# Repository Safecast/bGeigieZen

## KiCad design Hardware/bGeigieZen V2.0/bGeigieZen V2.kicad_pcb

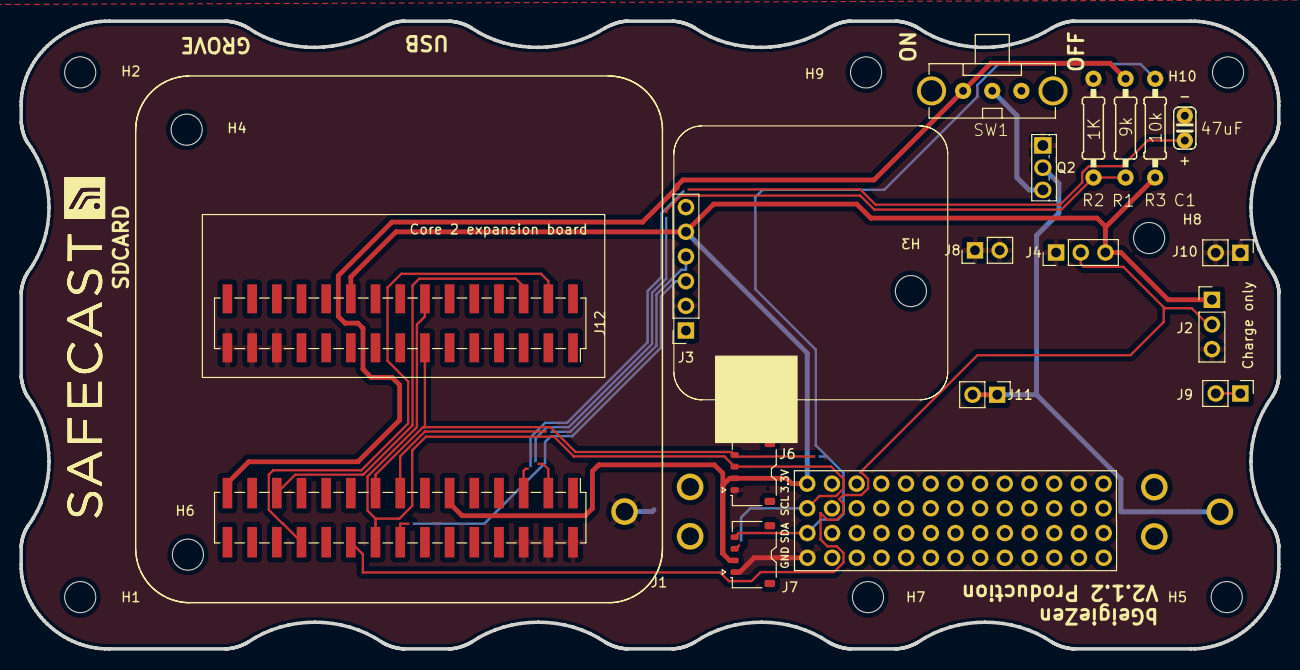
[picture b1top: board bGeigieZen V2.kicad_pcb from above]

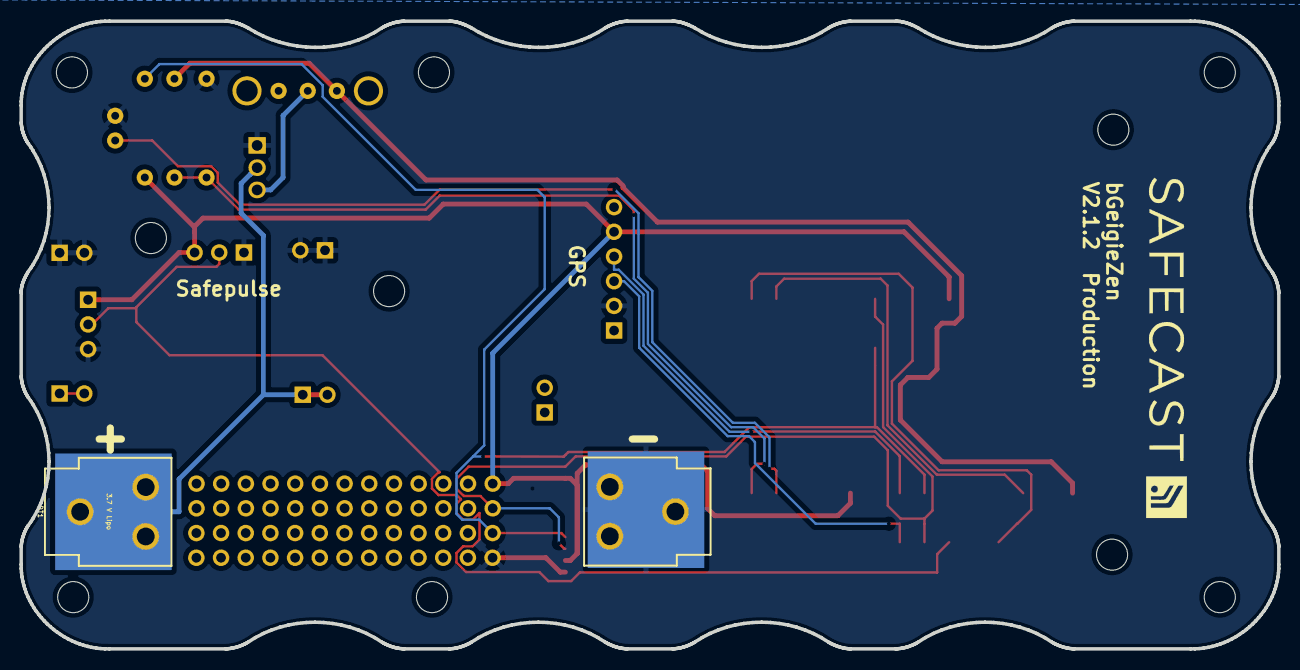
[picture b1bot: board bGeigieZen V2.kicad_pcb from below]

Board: 2 copper layers, 129.4 x 64.6 mm, 31 parts (2 on the bottom side), 15 nets.

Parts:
BT1: 3.7 V Lipo; BATTERY_18650-HOLDER
C1: 47uF; C025-024X044
H1, H2, H3, H4, H5, H6, H7, H8, H9, H10: MountingHole_Pad; MountingHole_3.2mm_M3
J1: M5 2x15 pin; PinHeader_2x15_P2.54mm_Vertical_SMD
J2: Geiger; PinHeader_1x03_P2.54mm_Vertical
J3: GPS; PinSocket_1x06_P2.54mm_Vertical
J4: Geiger 2; PinHeader_1x03_P2.54mm_Vertical
J5: Extra support header; PinHeader_1x02_P2.54mm_Vertical
J6, J7: Grove; JST_ACH_BM04B-ACHSS-A-GAN-ETF_1x04-1MP_P1.20mm_Vertical
J8: QI charger GND; PinHeader_1x02_P2.54mm_Vertical
J9: QI Plus; PinHeader_1x02_P2.54mm_Vertical
J10: QI GND; PinHeader_1x02_P2.54mm_Vertical
J11: QI charger Plus; PinHeader_1x02_P2.54mm_Vertical
J12: M5 2x15 pin; PinSocket_2x15_P2.54mm_Vertical_SMD
Q2: IRFU9024N; TO-251-3_Vertical
R1: 9k; 0207_10
R2: 1K; 0207_10
R3: 10k; 0207_10
SW1: SW_SPDT; EG1206
sea of pads 1, sea of pads 2: PinHeader_2x13_P2.54mm_Vertical

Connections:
3.3V: J1.11, J2.1, J3.5, J4.3, J6.2, J7.2, J12.20, R3.1, sea of pads 1.2
/BAT: J1.29, R1.1, SW1.3 (C)
/GIO2: J1.20, J2.2, J4.2
/GIO34: J1.25, J12.6
/RX2: J1.15, J3.4
/Reset: C1.1, J1.5
/SCL: J1.18, J6.3, J7.3, J12.14, sea of pads 1.1
/SDA: J1.17, J6.4, J7.4, J12.13, R3.2, sea of pads 2.2
/TX2: J1.16, J3.3
/VBATT: Q2.3, SW1.2 (B)
GND: BT1.2 (-), C1.2, J1.2, J1.4, J1.6, J2.3, J3.2, J4.1, J6.1, J7.1, J8.1, J8.2, J10.1, J10.2, J12.25, J12.27, J12.29, Q2.1, R2.2, sea of pads 2.1
unnamed: BT1.1 (+), J11.1, J11.2, Q2.2
unnamed: J1.3, R1.2, R2.1
unnamed: J1.24, J12.4
unnamed: J9.1, J9.2

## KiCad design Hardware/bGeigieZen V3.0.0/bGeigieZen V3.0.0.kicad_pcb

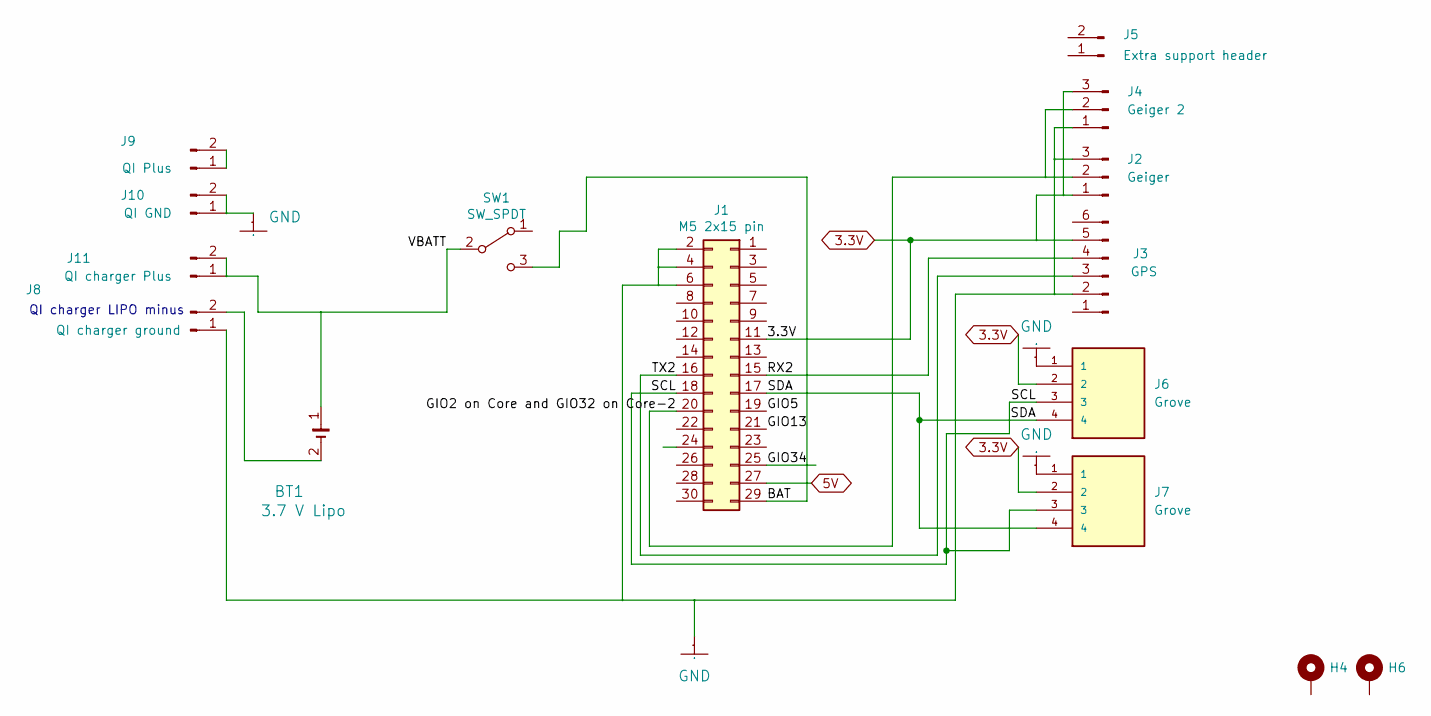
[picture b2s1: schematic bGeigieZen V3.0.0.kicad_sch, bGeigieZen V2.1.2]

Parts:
BT1: 3.7 V Lipo; BATTERY_18650-HOLDER
H4, H6: MountingHole_Pad; MountingHole_3.2mm_M3
J1: M5 2x15 pin; PinHeader_2x15_P2.54mm_Vertical_SMD
J2: Geiger; PinHeader_1x03_P2.54mm_Vertical
J3: GPS; PinSocket_1x06_P2.54mm_Vertical
J4: Geiger 2; PinHeader_1x03_P2.54mm_Vertical
J5: Extra support header; PinHeader_1x02_P2.54mm_Vertical
J6, J7: Grove; JST_ACH_BM04B-ACHSS-A-GAN-ETF_1x04-1MP_P1.20mm_Vertical; PARTREV A
J8: QI charger ground; PinHeader_1x02_P2.54mm_Vertical
J9: QI Plus; PinHeader_1x02_P2.54mm_Vertical
J10: QI GND; PinHeader_1x02_P2.54mm_Vertical
J11: QI charger Plus; PinHeader_1x02_P2.54mm_Vertical_4056
SW1: SW_SPDT; EG1206

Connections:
3.3V: J1.11, J2.1, J3.5, J4.3, J6.2, J7.2
5V: J1.27
/BAT: J1.29, SW1.3 (C)
/GIO2 on Core and GIO32 on Core-2: J1.20, J2.2, J4.2
/GIO5: J1.19
/GIO13: J1.21
/GIO34: J1.25
/RX2: J1.15, J3.4
/SCL: J1.18, J6.3, J7.3
/SDA: J1.17, J6.4, J7.4
/TX2: J1.16, J3.3
/VBATT: BT1.1 (+), J11.1, J11.2, SW1.2 (B)
GND: J1.2, J1.4, J1.6, J2.3, J3.2, J4.1, J6.1, J7.1, J8.1, J10.1, J10.2
unnamed: BT1.2 (-), J8.2
unnamed: J9.1, J9.2

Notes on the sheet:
QI charger LIPO minus

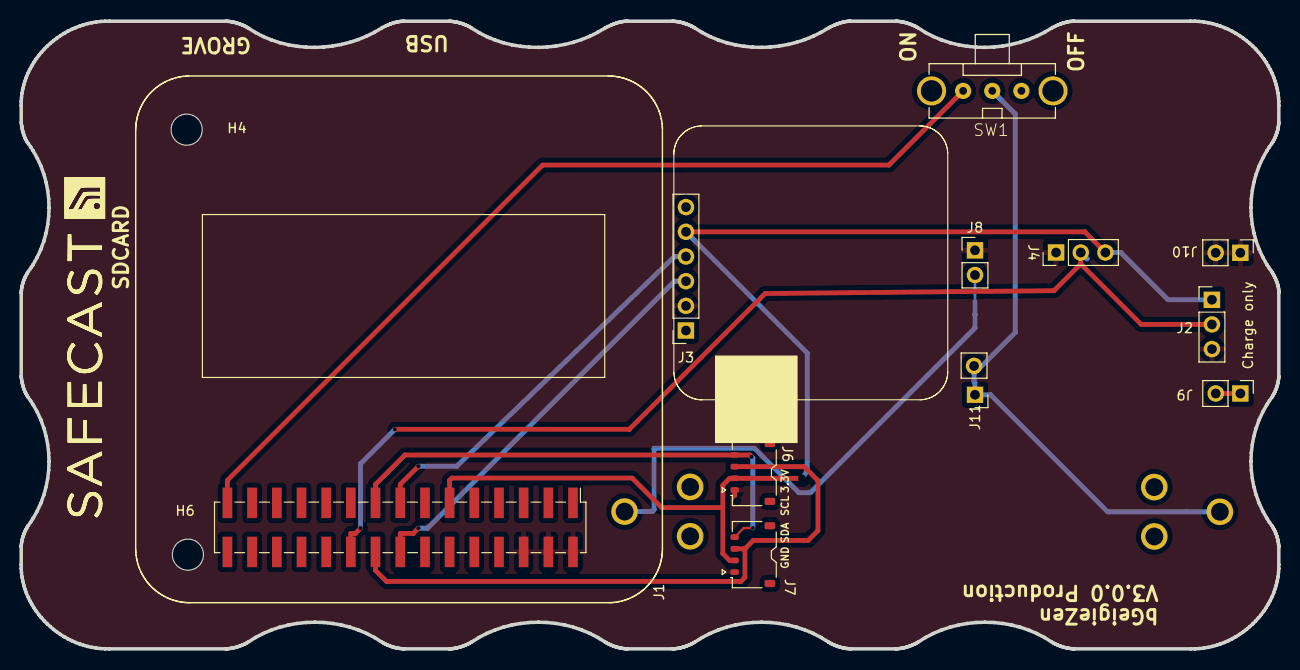
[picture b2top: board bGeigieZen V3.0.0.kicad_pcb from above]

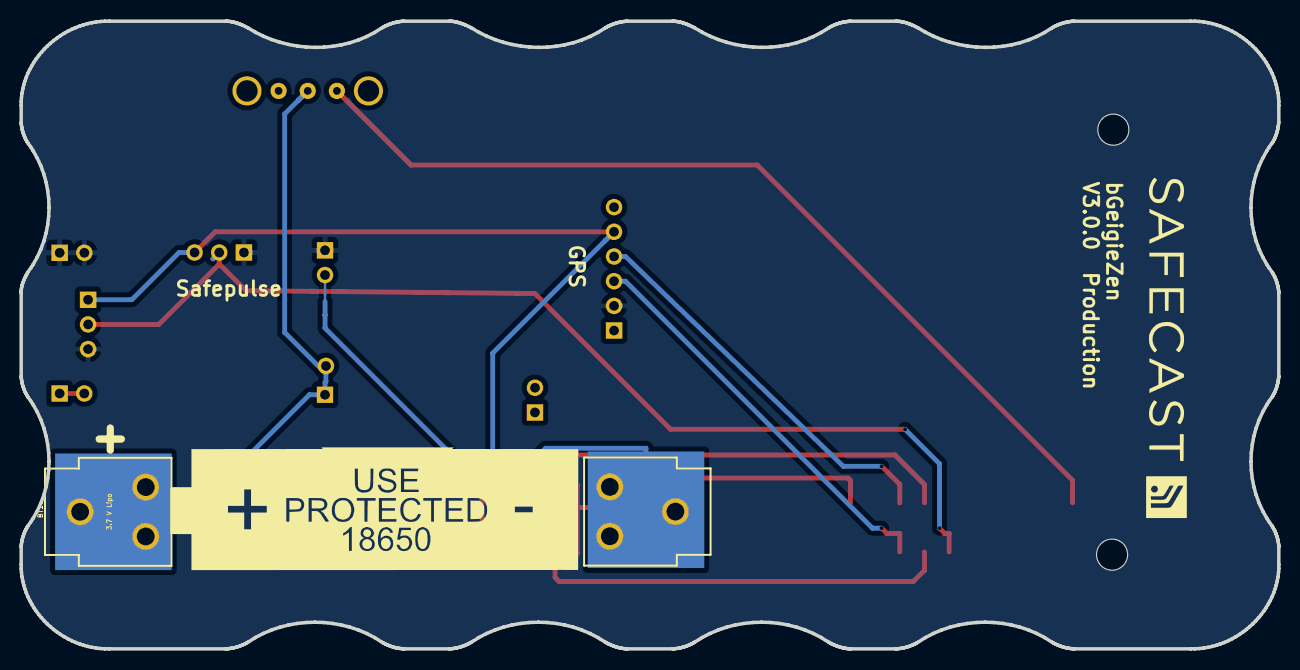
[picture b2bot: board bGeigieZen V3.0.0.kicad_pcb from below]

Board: 2 copper layers, 129.4 x 64.6 mm, 18 parts (3 on the bottom side), 11 nets.

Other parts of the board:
1850 LABEL: LOGO; 18650 map
G back: LOGO
G front: LOGO

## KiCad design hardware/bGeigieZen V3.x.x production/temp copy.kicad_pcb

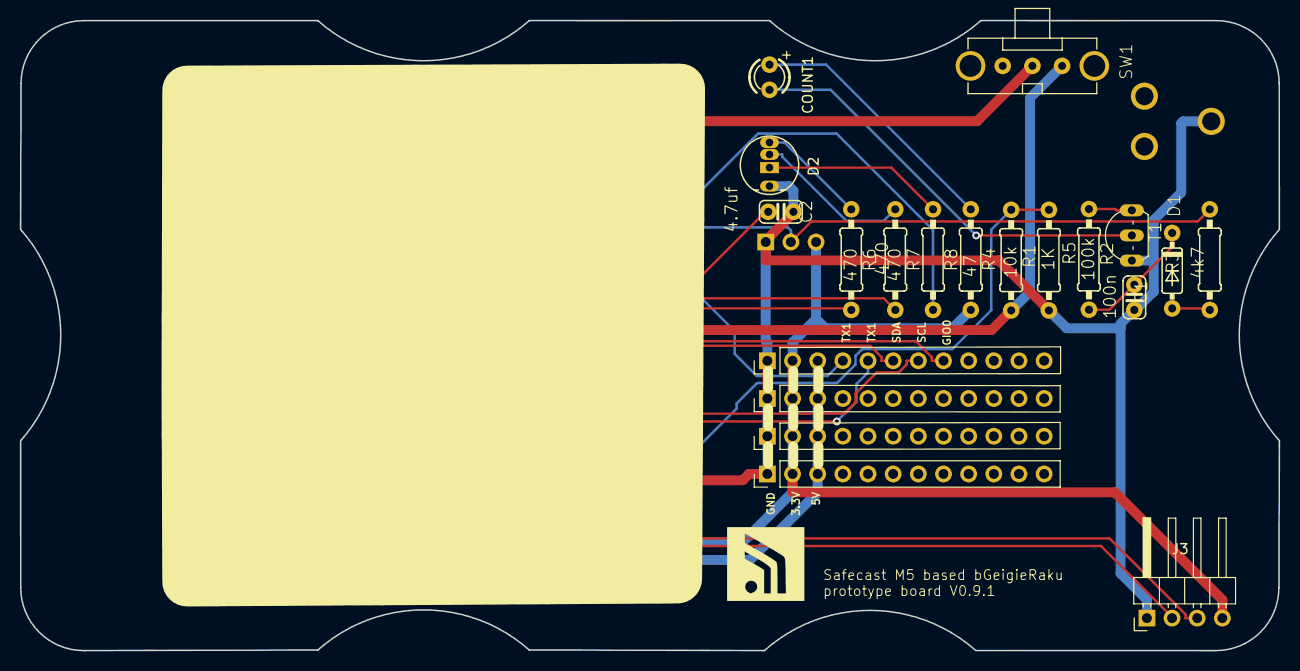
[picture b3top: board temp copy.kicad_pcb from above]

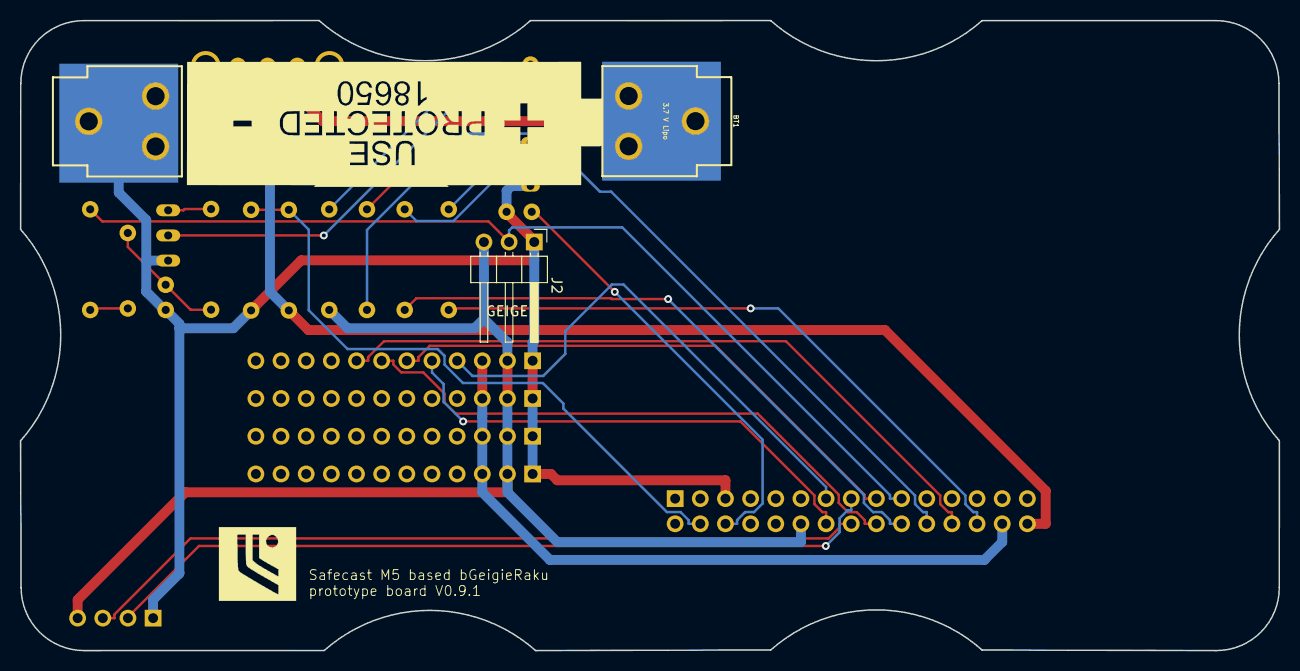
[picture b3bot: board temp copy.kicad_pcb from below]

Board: 2 copper layers, 127.1 x 63.6 mm, 25 parts (3 on the bottom side), 26 nets.

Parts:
BT1: 3.7 V Lipo; BATTERY_18650-HOLDER
C1: 100n; C025-024X044
C2: 4.7uf; C025-024X044
COUNT1: BLUE; LED3MM
D1: 1N4148; DO35-7
D2: LED_CRGB; LED-RGB-5MM_Common_Cathode
J1: M5 2x15 pin; PinHeader_2x15_P2.54mm_Vertical
J2: Geiger; PinHeader_1x03_P2.54mm_Horizontal
J3: GPS; PinHeader_1x04_P2.54mm_Horizontal
J4, J5, J6, J7: Conn_01x14_Female; PinHeader_1x14_P2.54mm_Vertical
Logo1: LOGO; safecast_logo_inverted
Logo 2: LOGO; safecast_logo_inverted
R1: 10k; 0207_10
R2: 1K; 0207_10
R3: 4k7; 0207_10
R4: 47; 0207_10
R5: 100k; 0207_10
R6, R7, R8: 470; 0207_10
SW1: SW_SPDT; EG1206
T1: 2SC1815; TO92-ECB

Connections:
3.3V: J1.12, J2.3, J3.4, J4.2, J5.2, J6.2, J7.2, R4.1
5V: J1.28, J4.3, J5.3, J6.3, J7.3
+5V: BT1.1, SW1.2
/GIO0: J1.24, J7.8
/GIO2: J1.19, J2.2, R3.1
/GIO5: J1.20, R7.2
/GIO13: J1.22, R8.2
/GIO34: J1.26, R6.2
/RX1: J1.14, J7.5
/RX2: J1.16, J3.3
/Reset: C2.1, J1.6
/SCL: J1.18, J7.7
/SDA: J1.17, J7.6
/TX1: J1.13, J7.4
/TX2: J1.15, J3.2
GND: BT1.2, C1.2, C2.2, D2.1, J1.5, J2.1, J3.1, J4.1, J5.1, J6.1, J7.1, R2.2, T1.E
unnamed: C1.1, D1.C, R5.1
unnamed: COUNT1.A, R4.2
unnamed: COUNT1.K, T1.C
unnamed: D1.A, R3.2
unnamed: D2.2, R8.1
unnamed: D2.3, R7.1
unnamed: D2.4, R6.1
unnamed: J1.4, R1.2, R2.1
unnamed: J1.30, R1.1, SW1.1
unnamed: R5.2, T1.B

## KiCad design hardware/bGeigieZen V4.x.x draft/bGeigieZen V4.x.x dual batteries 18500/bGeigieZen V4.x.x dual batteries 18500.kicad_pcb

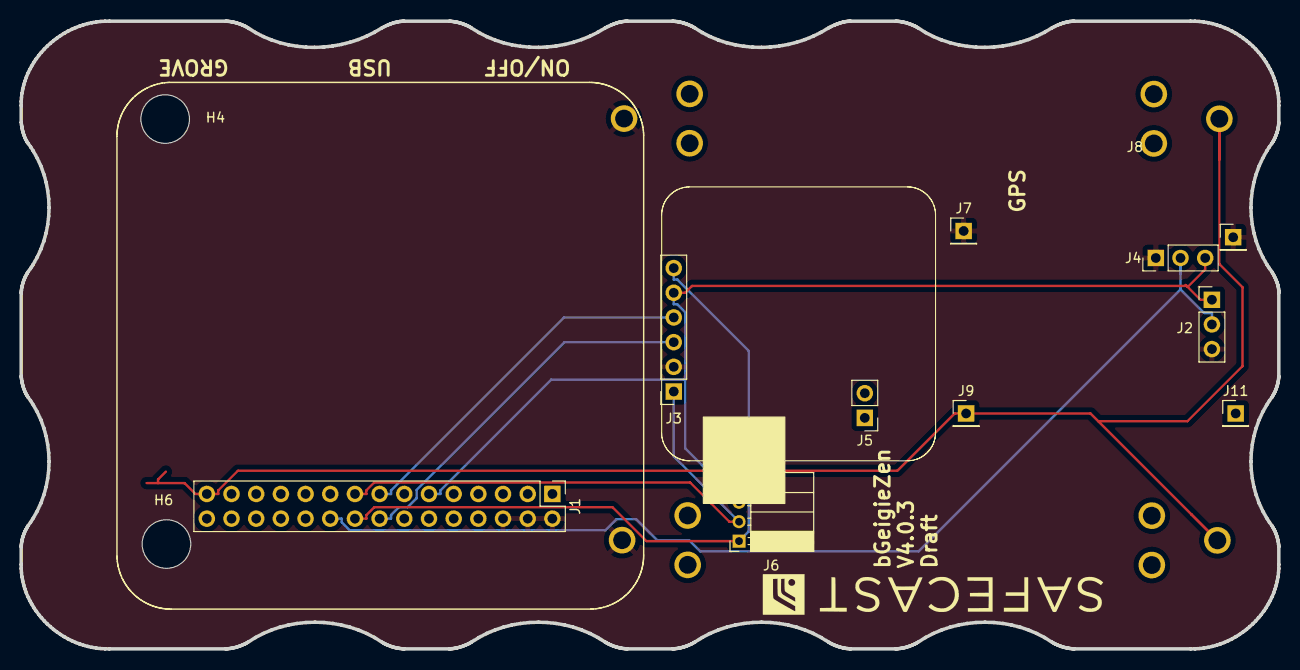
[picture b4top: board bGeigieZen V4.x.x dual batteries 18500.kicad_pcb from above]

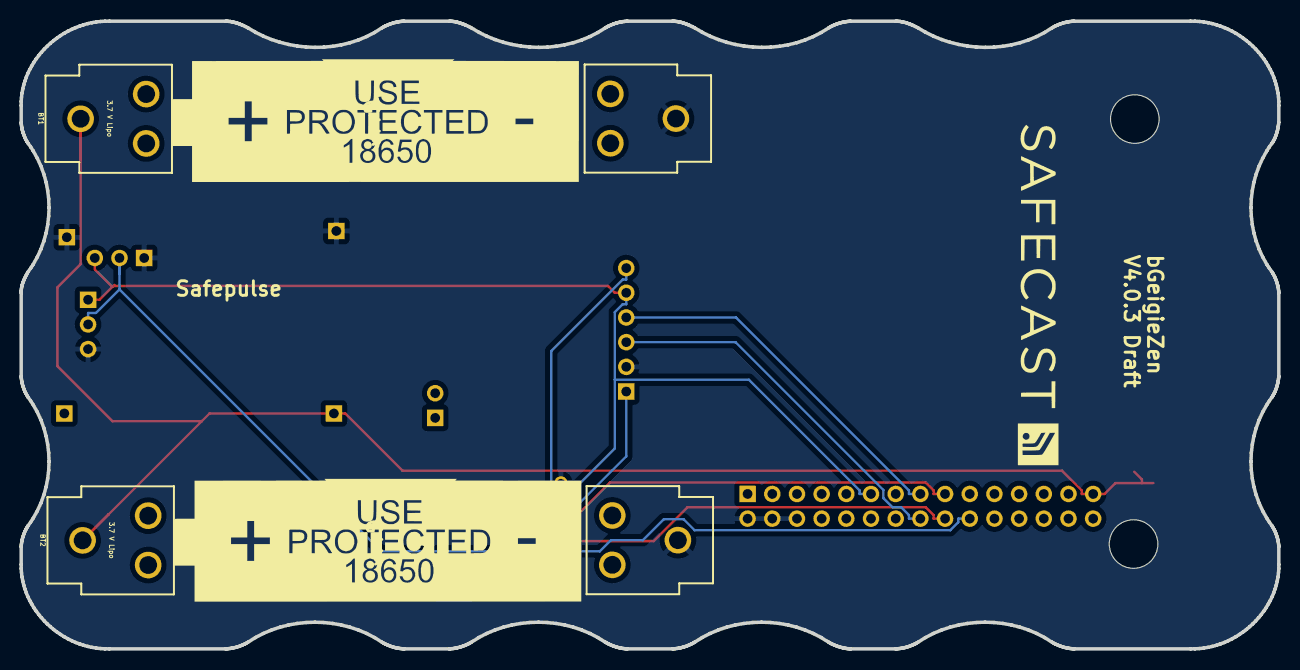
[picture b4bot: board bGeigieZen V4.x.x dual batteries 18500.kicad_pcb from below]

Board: 2 copper layers, 129.4 x 64.6 mm, 16 parts (3 on the bottom side), 8 nets.

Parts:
BT1, BT2: 3.7 V Lipo; BATTERY_18650-HOLDER
G back: LOGO
G front: LOGO
H4, H6: MountingHole_Pad; MountingHole_3.2mm_M3
J1: M5 2x15 pin; PinHeader_2x15_P2.54mm_Vertical
J2: Geiger IRover; PinHeader_1x03_P2.54mm_Vertical
J3: GPS; PinSocket_1x06_P2.54mm_Vertical
J4: Geiger Safepulse; PinHeader_1x03_P2.54mm_Vertical
J5: Extra support header; PinHeader_1x02_P2.54mm_Vertical
J6: Grove; PinSocket_1x04_P2.00mm_Horizontal
J7: QI GND out; PinHeader_1x01_P2.54mm_Vertical
J8: QI input GND; PinHeader_1x01_P2.54mm_Vertical
J9: QI battery out; PinHeader_1x01_P2.54mm_Vertical
J11: QI input +5V; PinHeader_1x01_P2.54mm_Vertical

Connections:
3.3V: J1.11, J2.1, J3.5, J4.3, J6.3
/BAT: BT1.1 (+), BT2.1 (+), J1.29, J9.1
/GIO2 on Core and GIO32 on Core-2: J1.20, J2.2, J4.2
/RX2: J1.15, J3.4
/SCL: J1.18, J3.6, J6.1
/SDA: J1.17, J3.1, J6.2
/TX2: J1.16, J3.3
GND: BT1.2 (-), BT2.2 (-), J1.2, J1.4, J1.6, J2.3, J3.2, J4.1, J6.4, J7.1, J8.1
